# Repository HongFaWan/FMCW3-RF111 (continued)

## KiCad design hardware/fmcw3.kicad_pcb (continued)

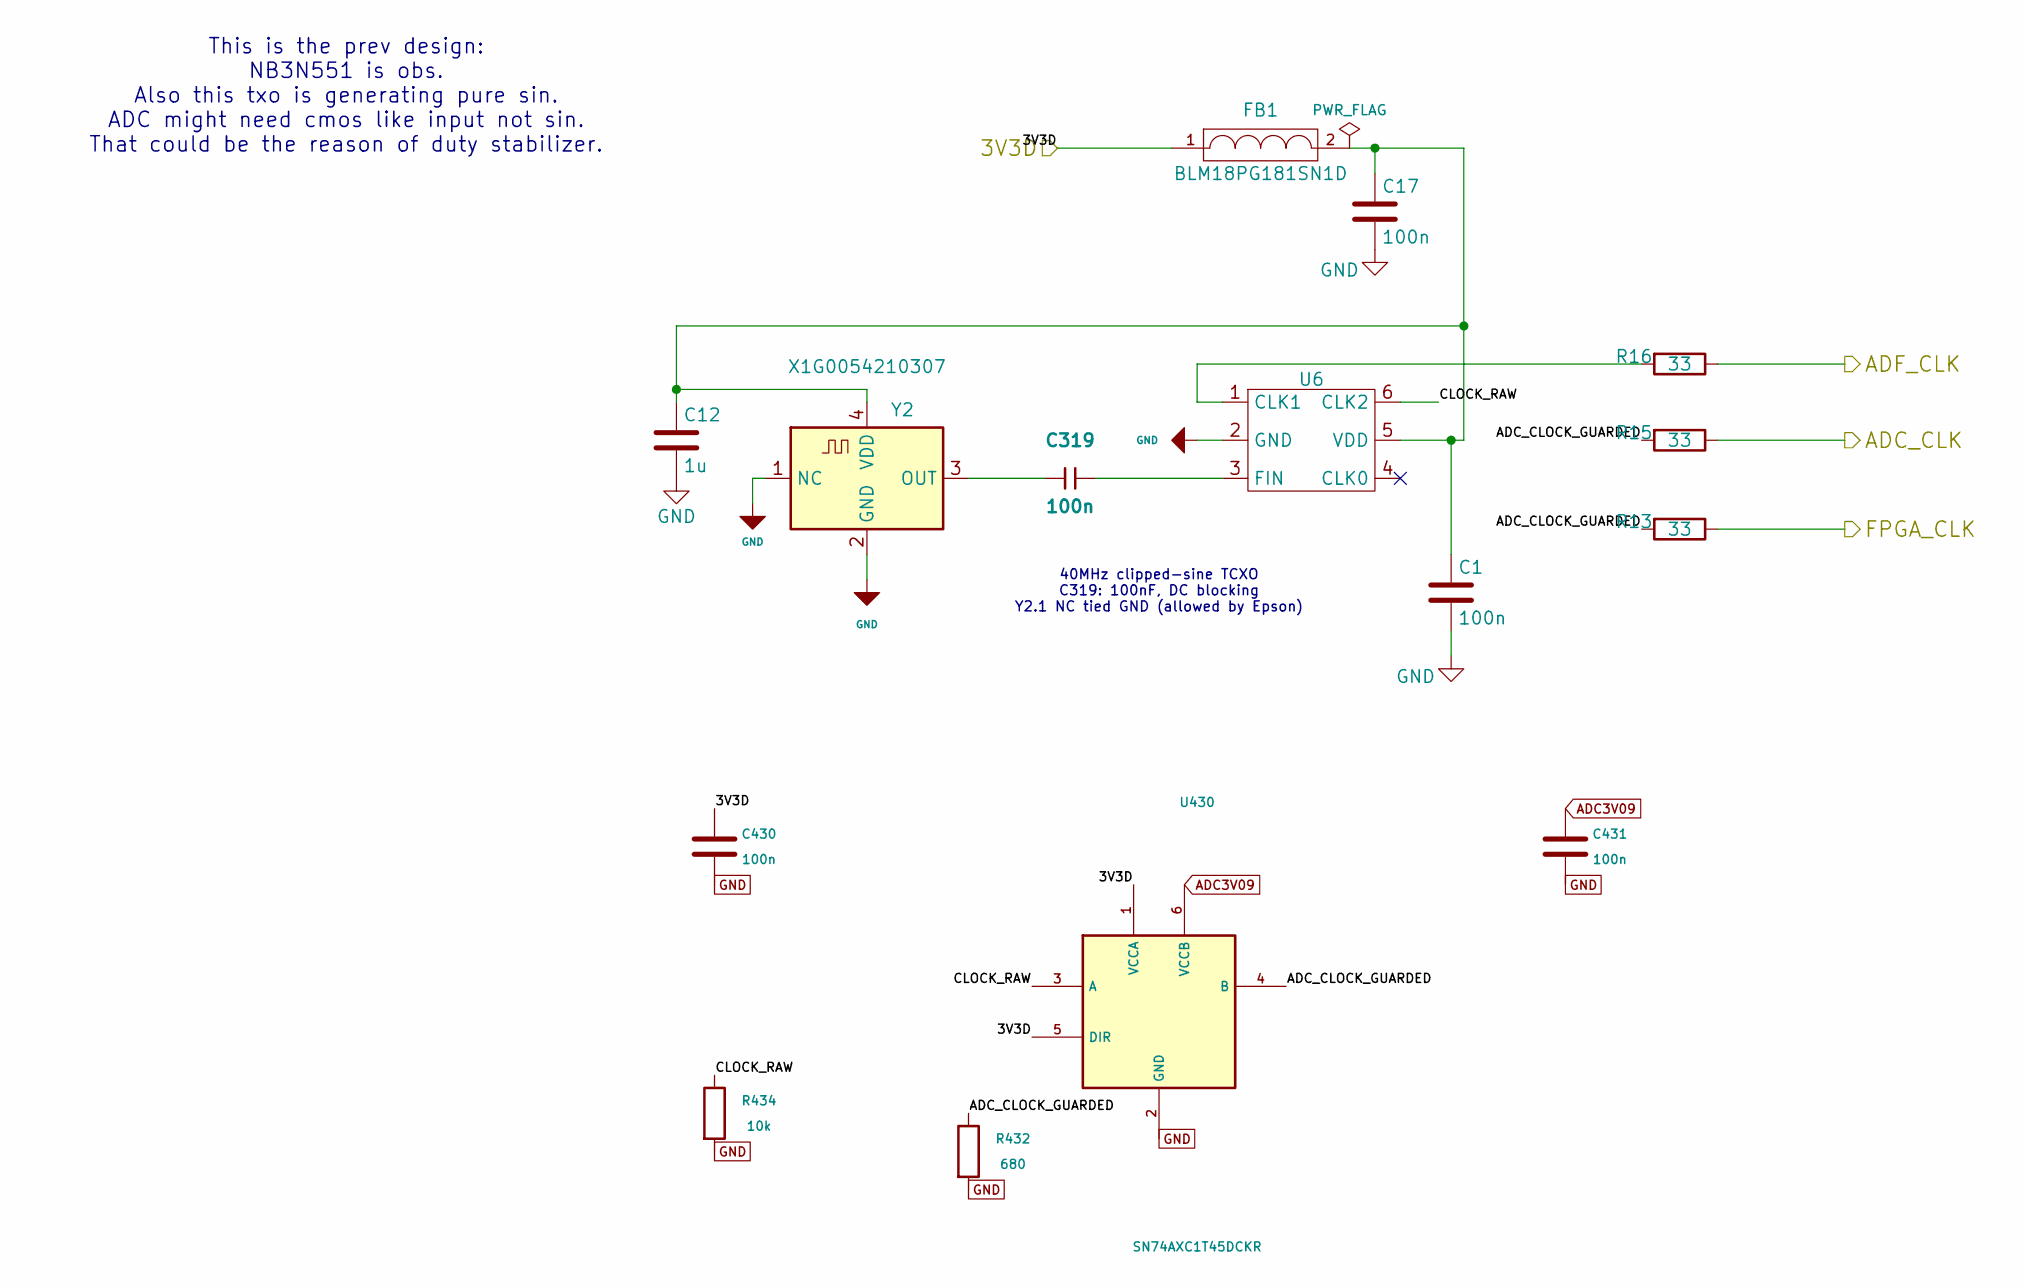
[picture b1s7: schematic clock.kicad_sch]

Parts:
C1, C17, C319: 100n; SMD_0402
C12: 1u; SMD_0603
C430, C431: 100n; SMD_0402; Voltage 50V; Tolerance 10%; MPN GRM155R71H104KE14D; LCSC C77020
FB1: BLM18PG181SN1D; SMD_0603
R13, R15, R16: 33; SMD_0402
R432: 680; R0402_Yageo_Mount_V10; MPN RC0402FR-07680RL; LCSC C137948
R434: 10k; R0402_Yageo_Mount_V10; MPN RT0402BRD0710KL; LCSC C190095
U6: PL133-37; SOT23_6
U430: SN74AXC1T45DCKR; TI_DCK6_0p9x0p4_MFR; MPN SN74AXC1T45DCKR; LCSC C2677392
Y2: X1G0054210307; TG2520SMN_MFR

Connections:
/ADC_CLK: R15.1; also elsewhere on the board
/ADF_CLK_REF: R16.1; also elsewhere on the board
/FPGA_CLK: R13.1; also elsewhere on the board
/clock/ADC_CLOCK_GUARDED: R13.2, R15.2, R432.1, U430.4 (B)
/clock/CLOCK_RAW: R434.1, U6.6 (CLK2), U430.3 (A)
ADC3V09: C431.1, U430.6 (VCCB); also elsewhere on the board
GND: C1.2, C12.2, C17.2, C430.2, C431.2, R432.2, R434.2, U6.2 (GND), U430.2 (GND), Y2.1 (NC), Y2.2 (GND); also elsewhere on the board
unnamed: R16.2, U6.1 (CLK1)
unnamed: C319.2, U6.3 (FIN)
unnamed: C1.1, C12.1, C17.1, FB1.2, U6.5 (VDD), Y2.4 (VDD)
unnamed: C319.1, Y2.3 (OUT)

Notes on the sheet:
40MHz clipped-sine TCXO C319: 100nF, DC blocking Y2.1 NC tied GND (allowed by Epson)
This is the prev design: NB3N551 is obs. Also this txo is generating pure sin. ADC might need cmos like input not sin. That could be the reason of duty stabilizer.

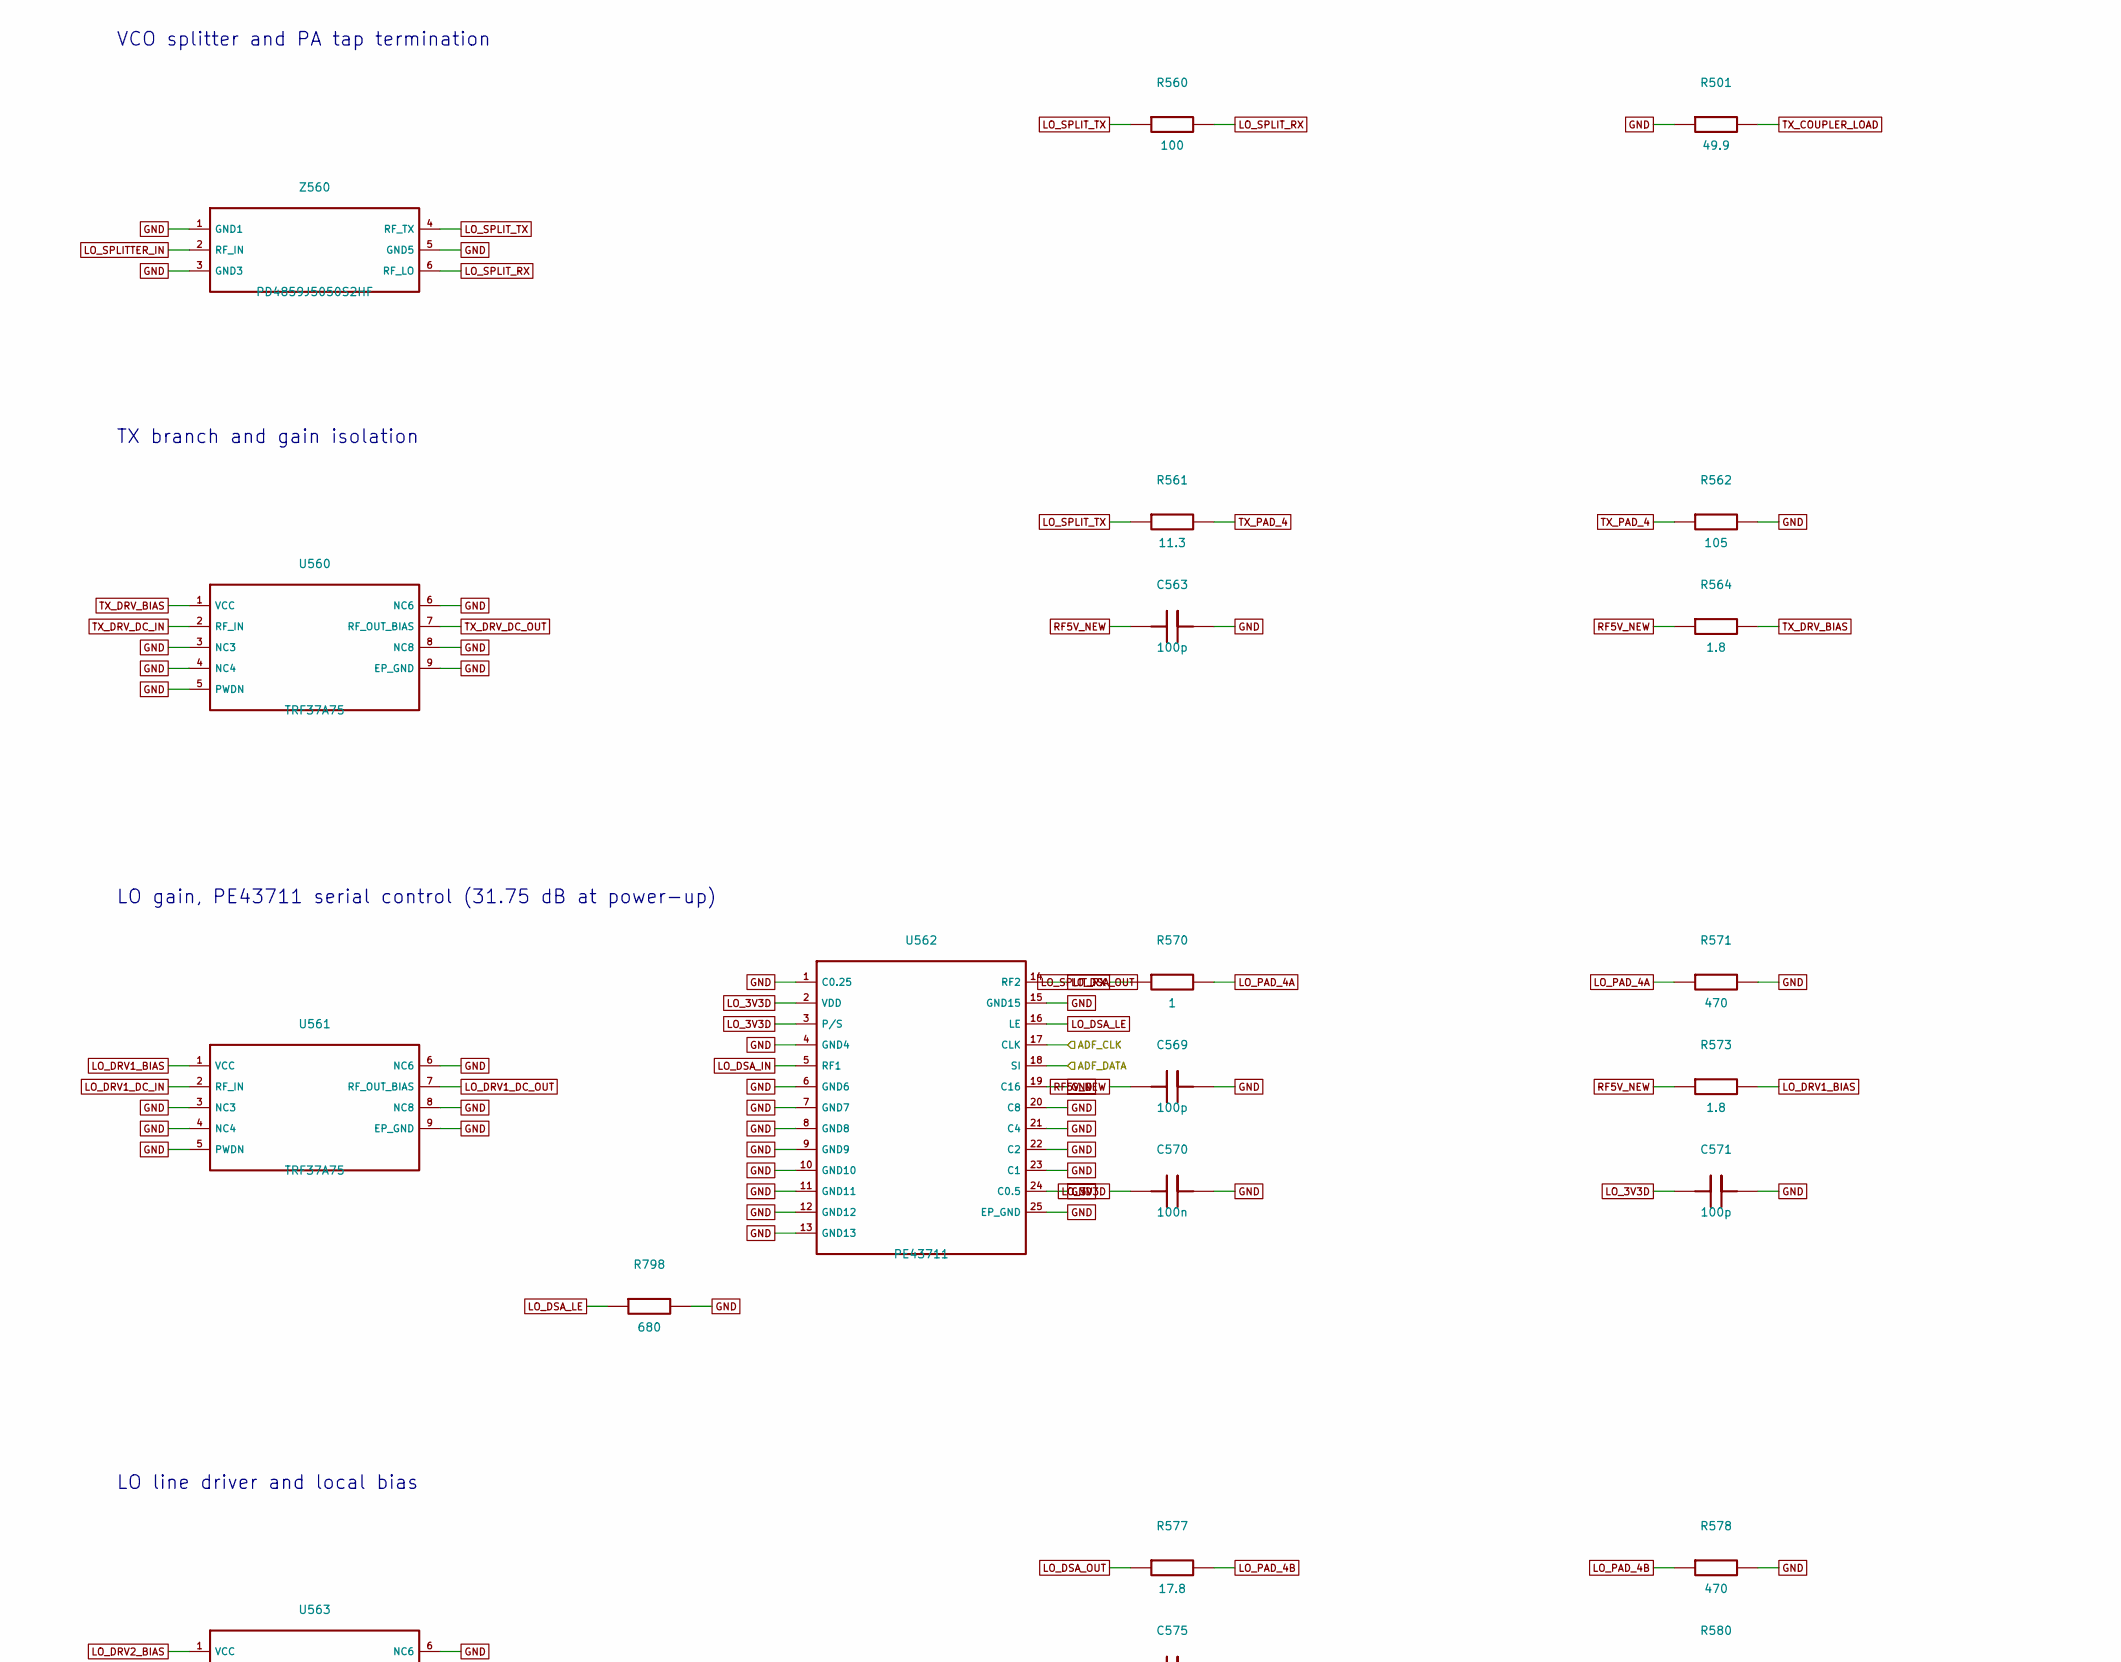
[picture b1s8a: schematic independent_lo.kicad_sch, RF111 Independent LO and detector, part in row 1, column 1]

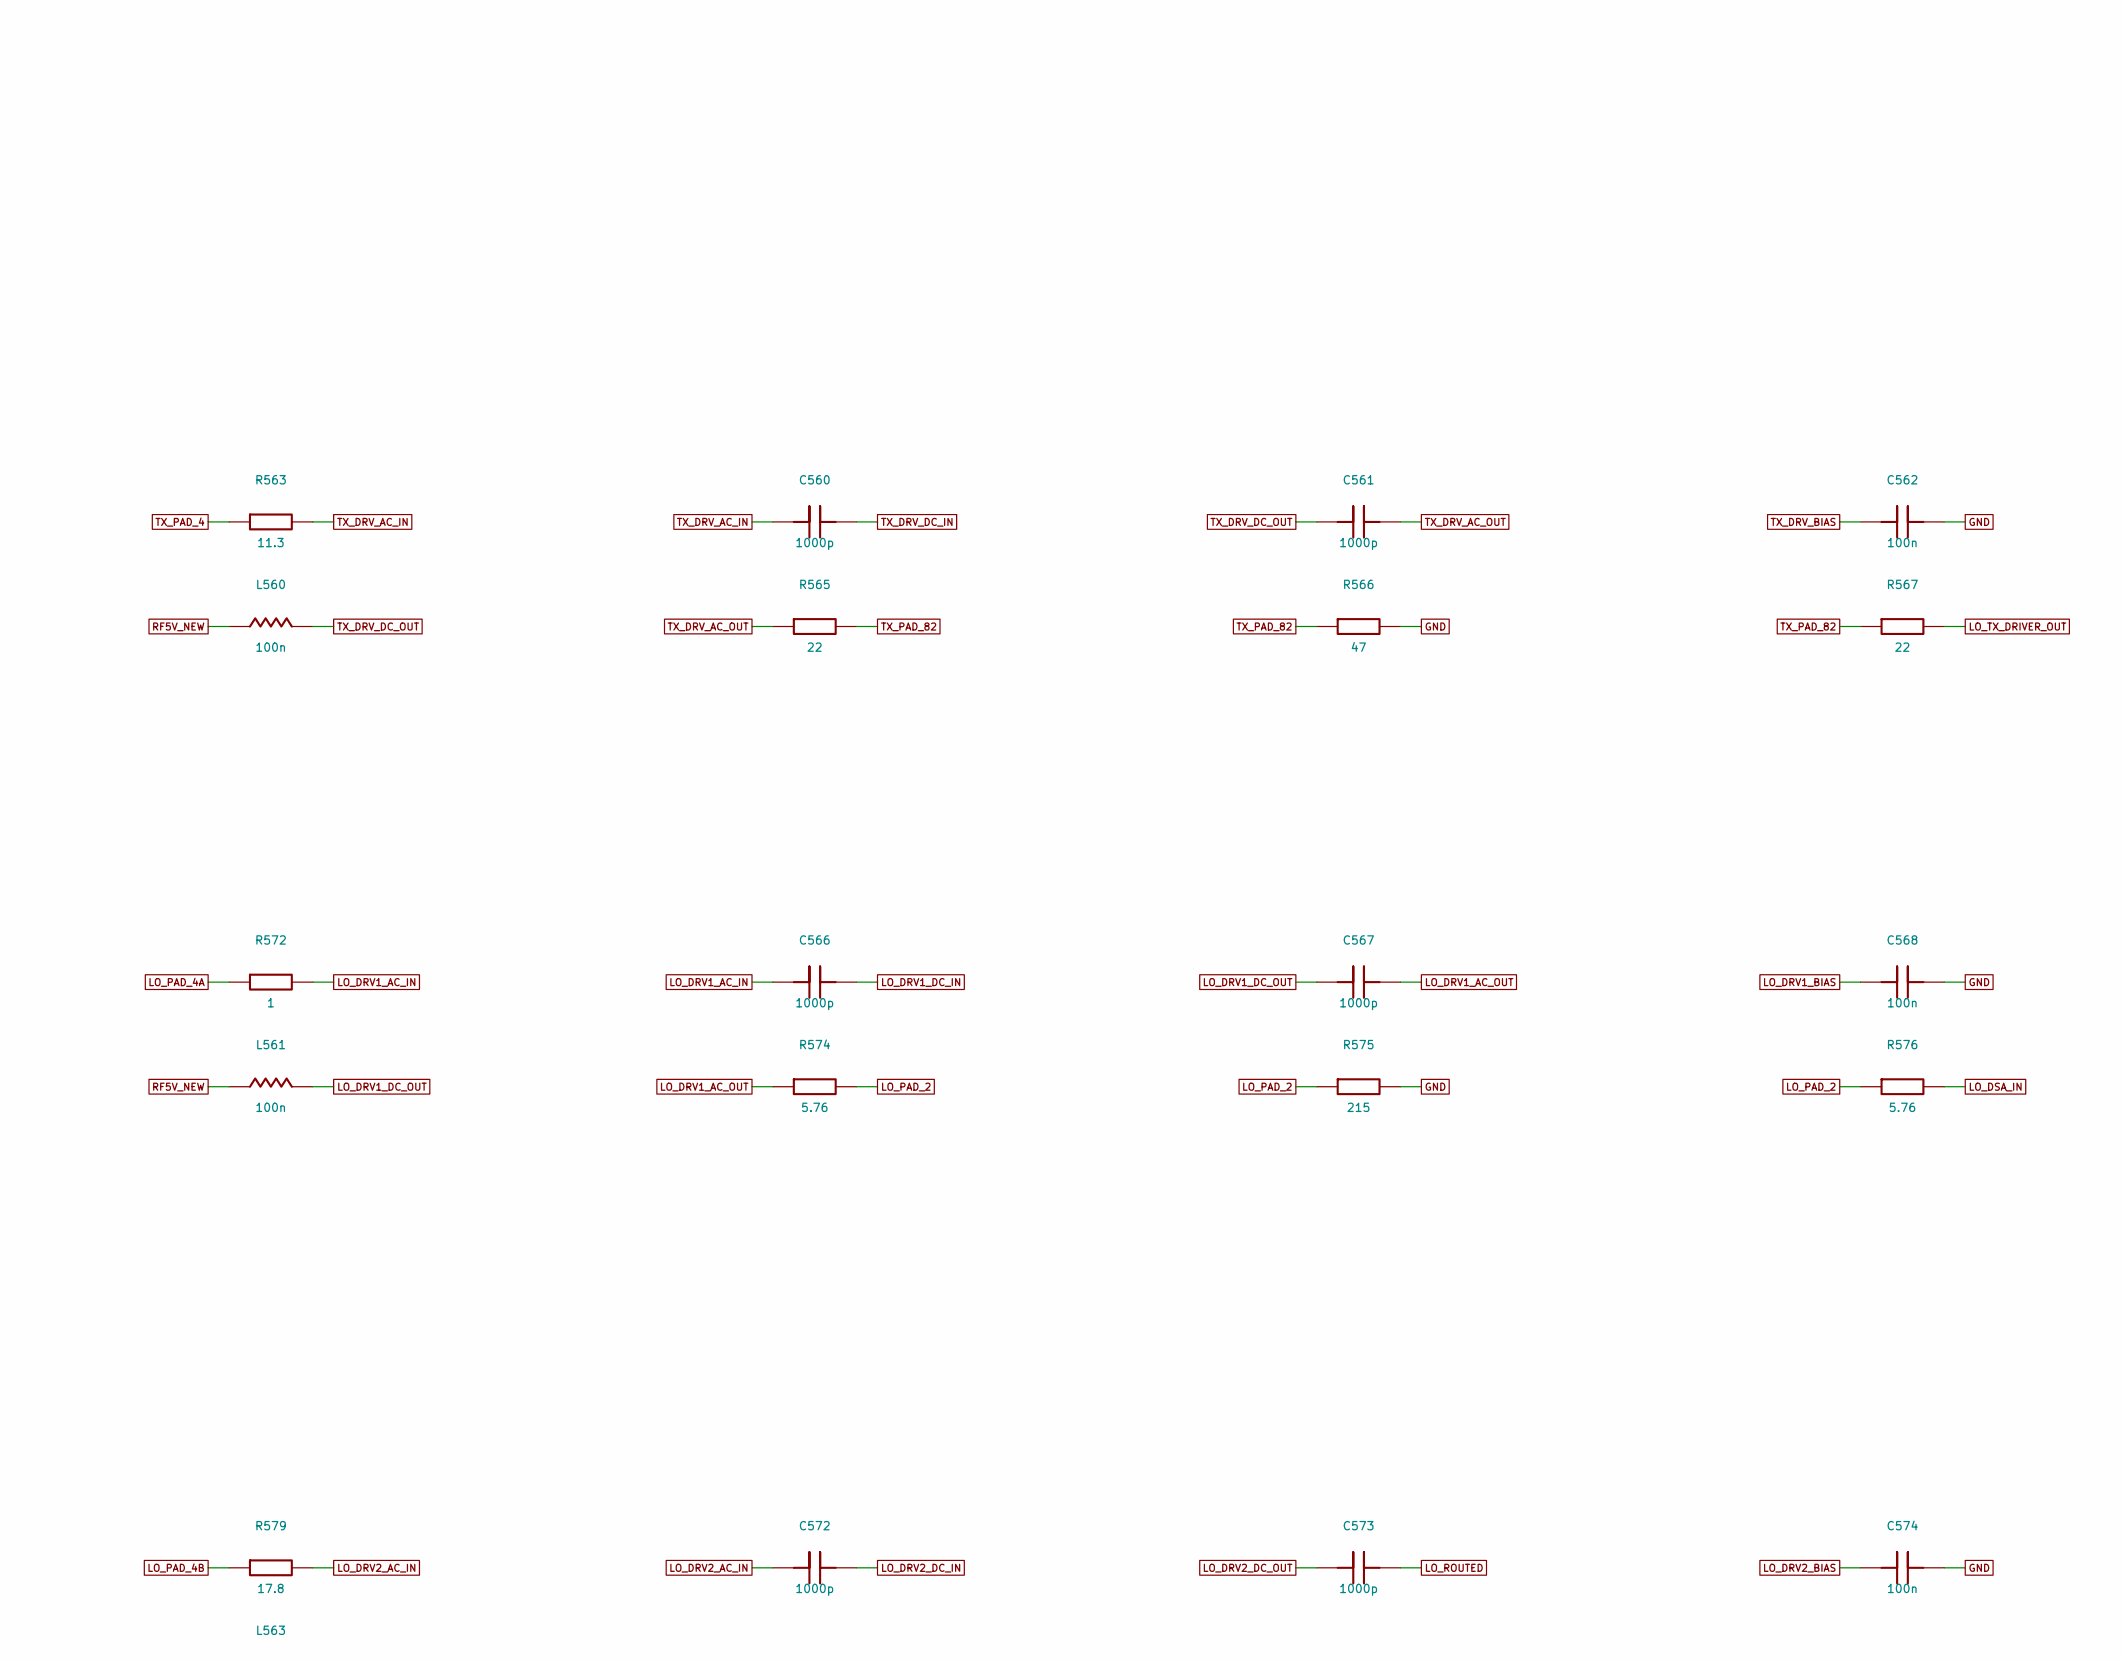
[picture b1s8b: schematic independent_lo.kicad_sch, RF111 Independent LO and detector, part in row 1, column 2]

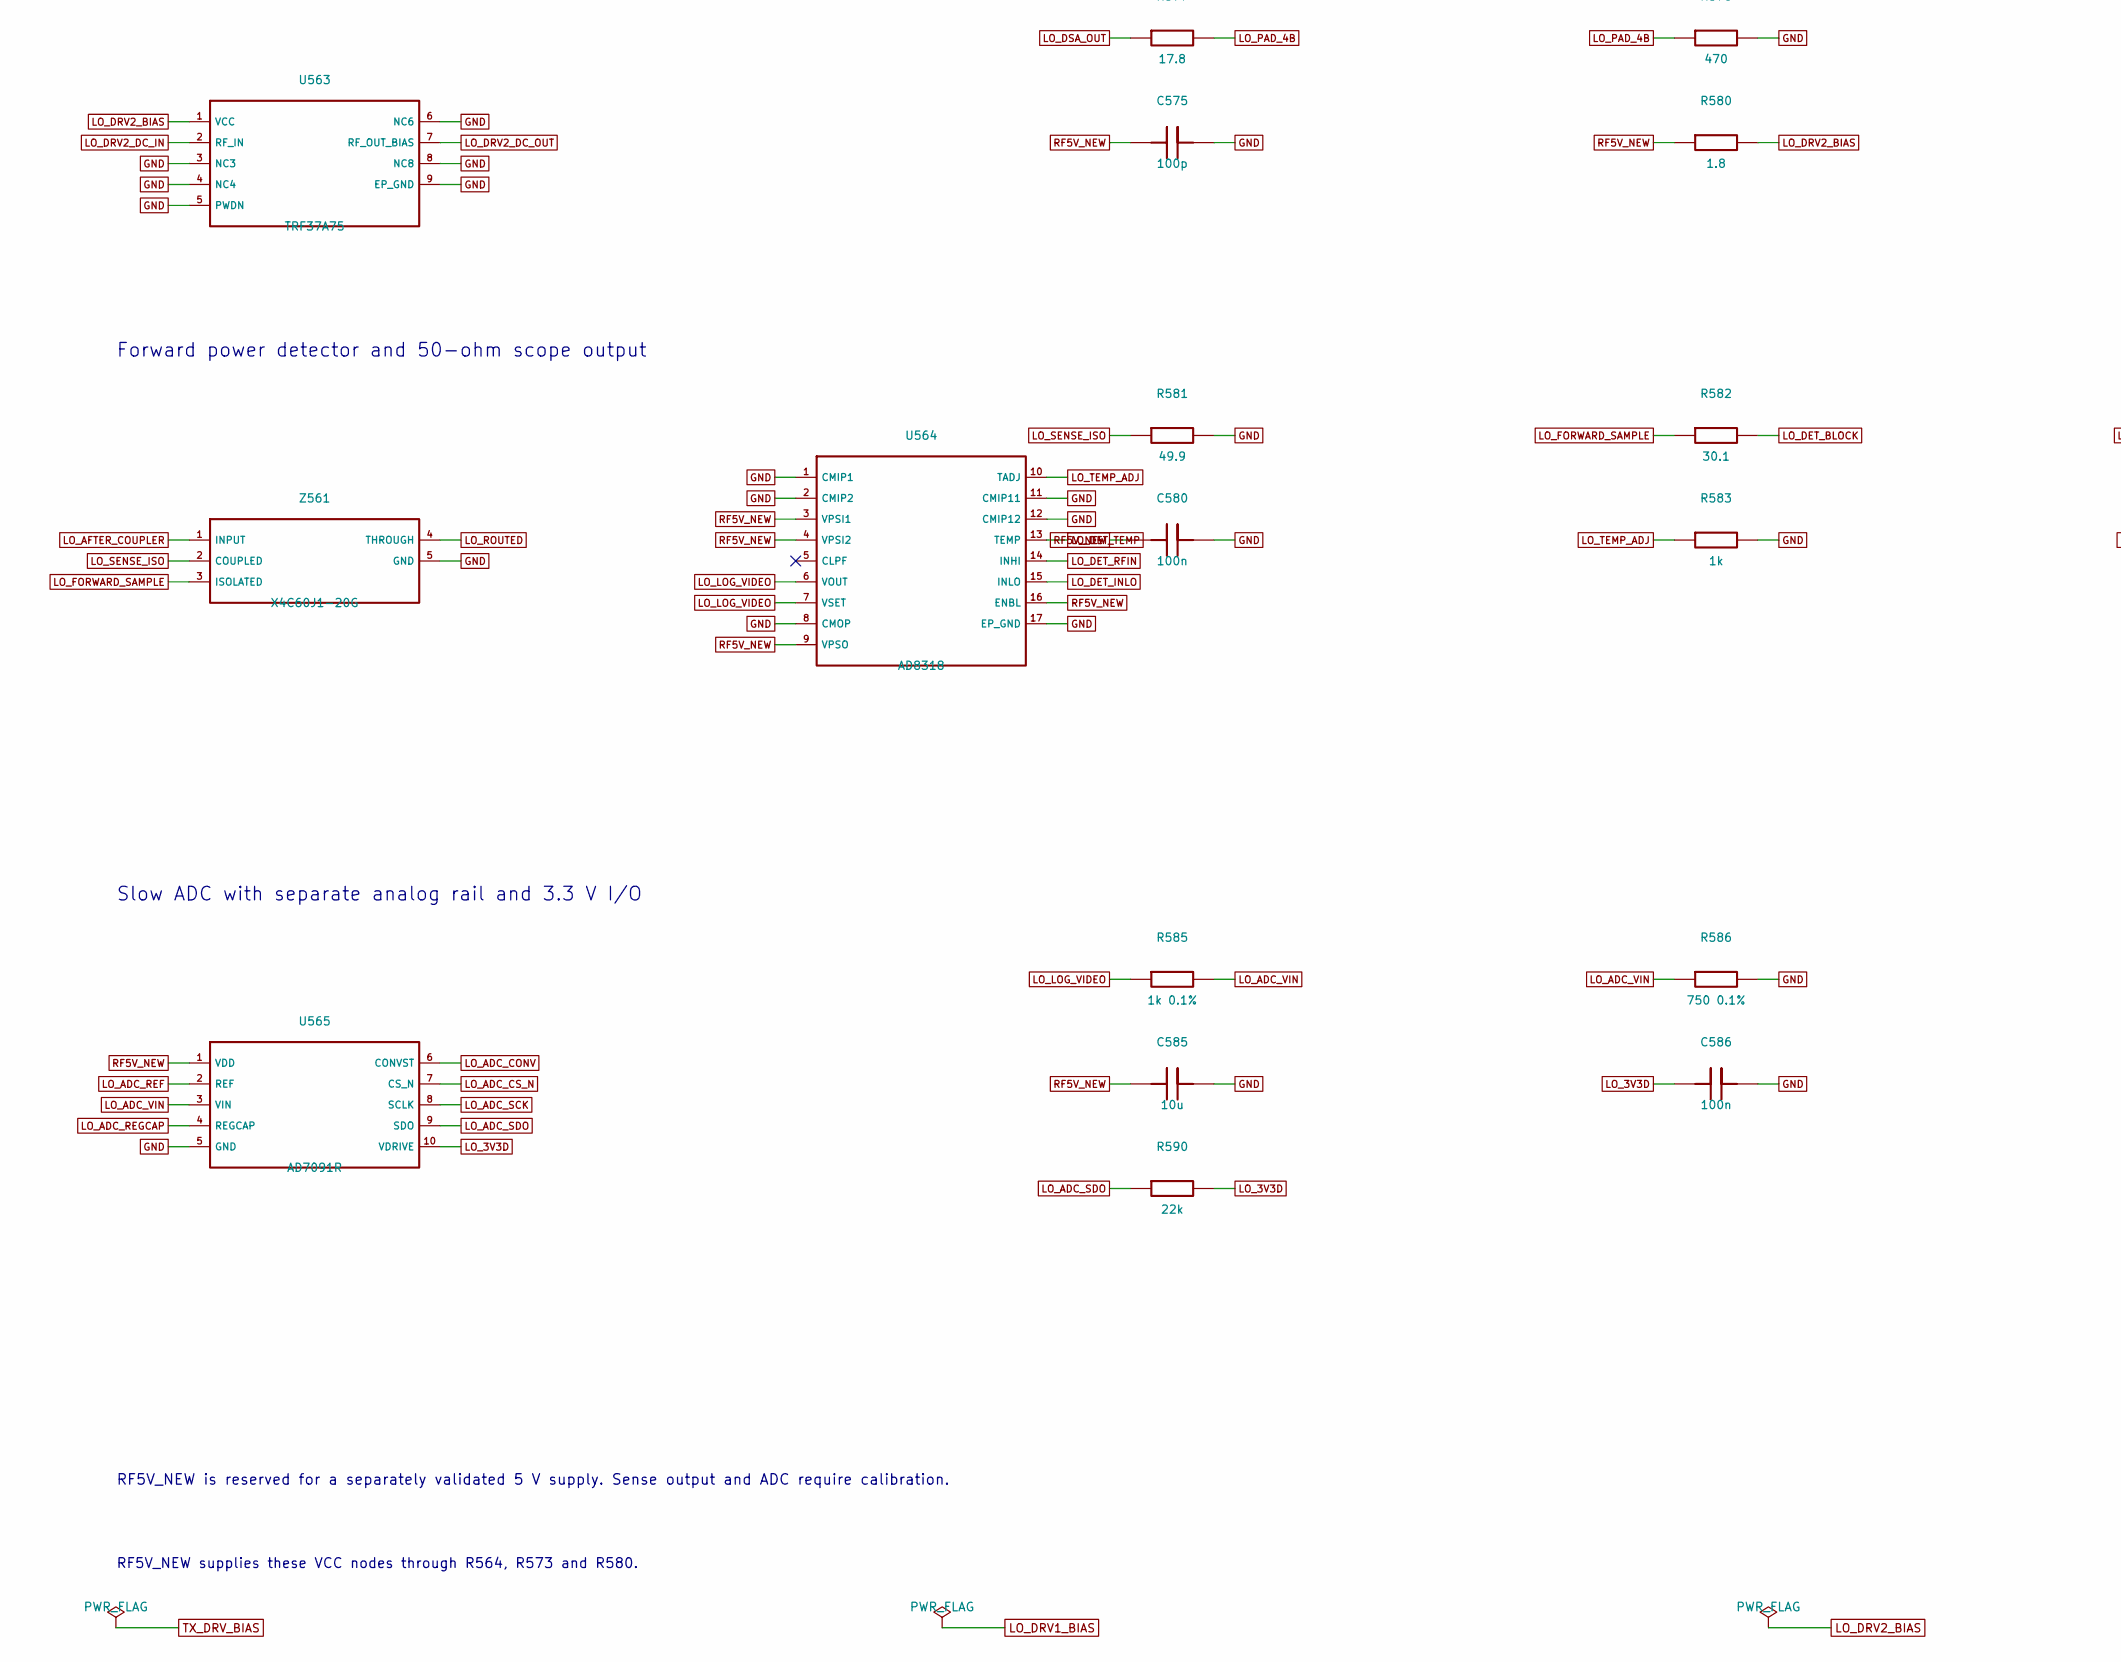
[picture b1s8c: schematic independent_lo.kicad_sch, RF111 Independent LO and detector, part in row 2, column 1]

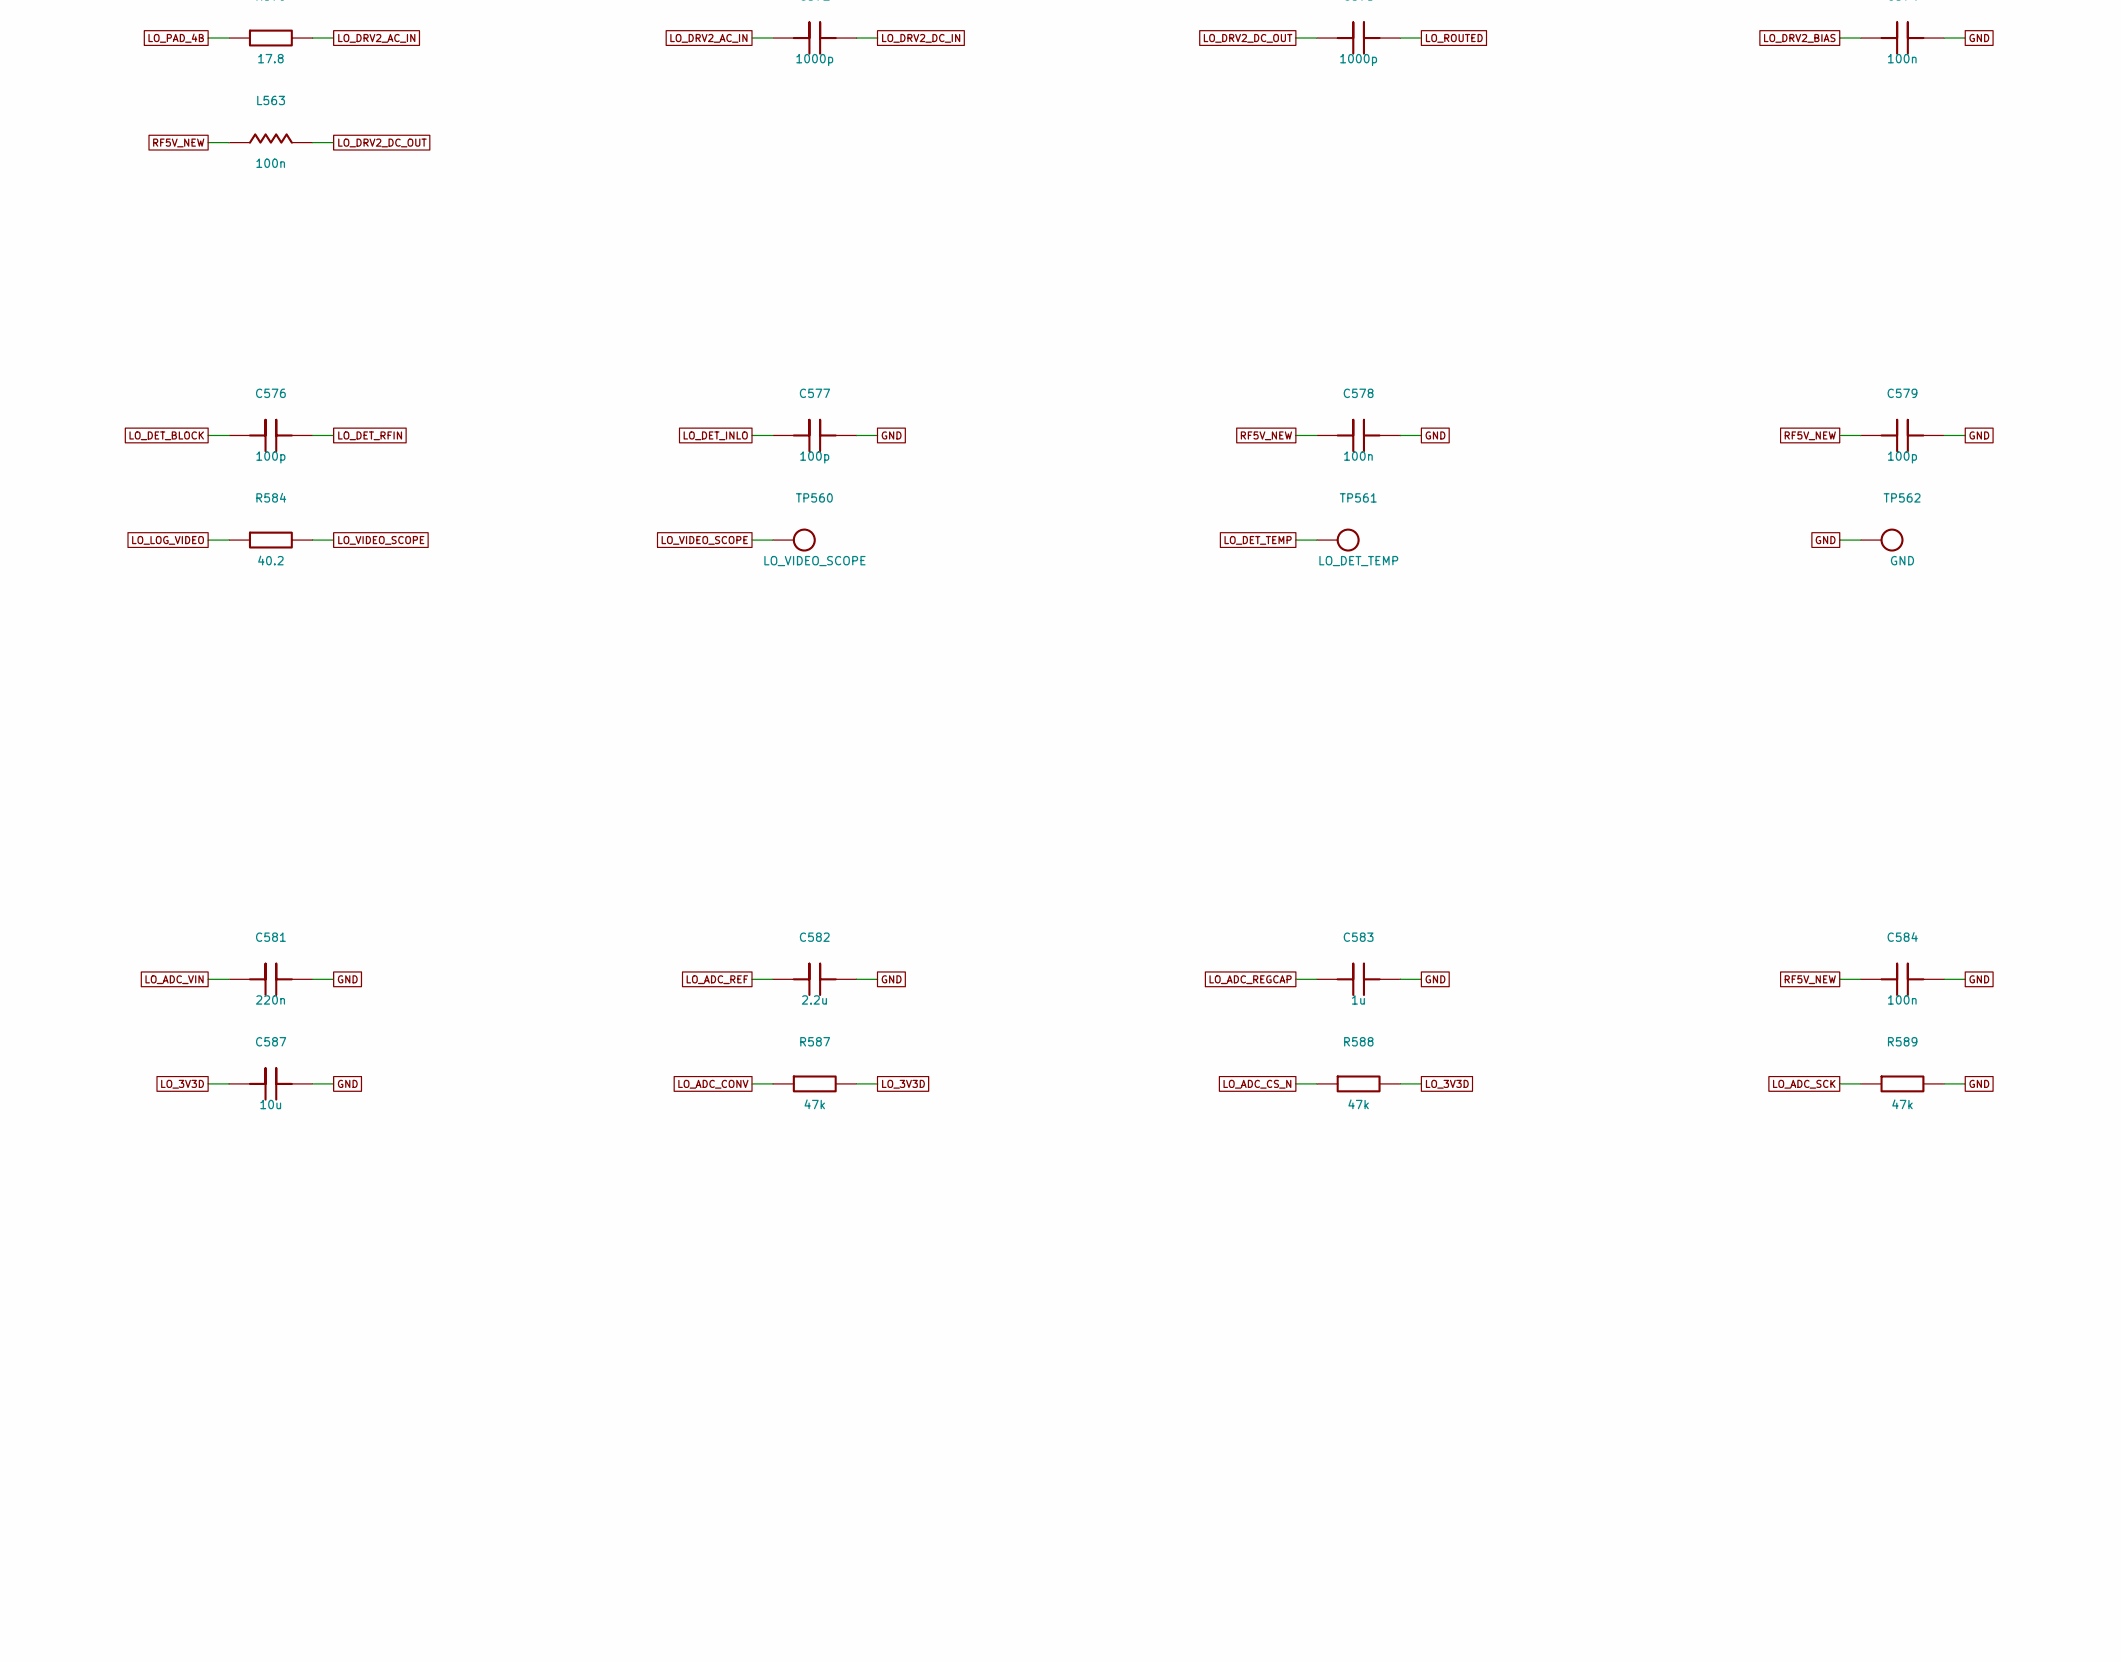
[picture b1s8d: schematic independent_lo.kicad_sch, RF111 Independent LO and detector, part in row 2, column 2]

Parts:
C560, C561, C566, C567, C572, C573: 1000p; C_0402_1005Metric; MPN GRM1555C1H102JA01D
C562, C568, C570, C574, C578, C580, C584, C586: 100n; C_0402_1005Metric; MPN GRM155R71H104KE14D
C563, C569, C571, C575, C576, C577, C579: 100p; C_0402_1005Metric; MPN GRM1555C1H101JA01D
C581: 220n; C_0402_1005Metric; MPN GRM155R71C224KA12D
C582: 2.2u; C_0603_1608Metric; MPN GRM188R71A225KE15D
C583: 1u; C_0603_1608Metric; MPN GRM188R71A105KA61D
C585, C587: 10u; C_0805_2012Metric; MPN GRM21BR61E106KA73L
L560, L561, L563: 100n; L_0402_1005Metric; MPN 0402HPH-R10XGRW
R501: 49.9; SMD_0402; MPN RC0402FR-0749R9L
R560: 100; R_0603_1608Metric; MPN RC0603FR-07100RL
R561, R563: 11.3; R_0402_1005Metric; MPN RC0402FR-0711R3L
R562: 105; R_0402_1005Metric; MPN RC0402FR-07105RL
R564, R573, R580: 1.8; R_0402_1005Metric; MPN RC0402FR-071R8L
R565, R567: 22; R_0402_1005Metric; MPN RC0402FR-0722RL
R566: 47; R_0402_1005Metric; MPN RT0402BRD0747RL
R570, R572: 1; R_0402_1005Metric; MPN RC0402FR-071RL
R571, R578: 470; R_0402_1005Metric; MPN RC0402FR-07470RL
R574, R576: 5.76; R_0402_1005Metric; MPN RC0402FR-075R76L
R575: 215; R_0402_1005Metric; MPN RC0402FR-07215RL
R577, R579: 17.8; R_0402_1005Metric; MPN RC0402FR-0717R8L
R581: 49.9; R_0402_1005Metric; MPN RC0402FR-0749R9L
R582: 30.1; R_0402_1005Metric; MPN RC0402FR-0730R1L
R583: 1k; R_0402_1005Metric; MPN RT0402BRD071KL
R584: 40.2; R_0402_1005Metric; MPN RC0402FR-0740R2L
R585: 1k 0.1%; R_0402_1005Metric; MPN ERA-2AEB102X
R586: 750 0.1%; R_0402_1005Metric; MPN ERA-2AEB751X
R587, R588, R589: 47k; R_0402_1005Metric; MPN RC0402FR-0747KL
R590: 22k; R_0402_1005Metric; MPN RC0402FR-0722KL
R798: 680; R_0402_Yageo_Mount22; MPN RC0402FR-07680RL; LCSC C137948
TP560: LO_VIDEO_SCOPE; TestPoint_Pad_D1.0mm
TP561: LO_DET_TEMP; TestPoint_Pad_D1.0mm
TP562: GND; TestPoint_Pad_D1.0mm
U560, U561, U563: TRF37A75; TI_DSG0008A; MPN TRF37A75IDSGR
U562: PE43711; pSemi_PE43711_QFN24; MPN PE43711B-Z
U564: AD8318; ADI_CP-16-59; MPN AD8318ACPZ-REEL7
U565: AD7091R; MSOP-10_3x3mm_P0.5mm; MPN AD7091RBRMZ-RL7
Z560: PD4859J5050S2HF; MPN PD4859J5050S2HF
Z561: X4C60J1-20G; MPN X4C60J1-20G

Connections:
/ADF_CLK: U562.17 (CLK); also elsewhere on the board
/ADF_DATA: U562.18 (SI); also elsewhere on the board
GND: C562.2, C563.2, C568.2, C569.2, C570.2, C571.2, C574.2, C575.2, C577.2, C578.2, C579.2, C580.2, C581.2, C582.2, C583.2, C584.2, C585.2, C586.2, C587.2, R501.1, R562.2, R566.2, R571.2, R575.2, R578.2, R581.2, R583.2, R586.2, R589.2, R798.2, TP562.1, U560.3 (NC3), U560.4 (NC4), U560.5 (PWDN), U560.6 (NC6), U560.8 (NC8), U560.9 (EP_GND), U561.3 (NC3), U561.4 (NC4), U561.5 (PWDN), U561.6 (NC6), U561.8 (NC8), U561.9 (EP_GND), U562.1 (C0.25), U562.4 (GND4), U562.6 (GND6), U562.7 (GND7), U562.8 (GND8), U562.9 (GND9), U562.10 (GND10), U562.11 (GND11), U562.12 (GND12), U562.13 (GND13), U562.15 (GND15), U562.19 (C16), U562.20 (C8), U562.21 (C4), U562.22 (C2), U562.23 (C1), U562.24 (C0.5), U562.25 (EP_GND), U563.3 (NC3), U563.4 (NC4), U563.5 (PWDN), U563.6 (NC6), U563.8 (NC8), U563.9 (EP_GND), U564.1 (CMIP1), U564.2 (CMIP2), U564.8 (CMOP), U564.11 (CMIP11), U564.12 (CMIP12), U564.17 (EP_GND), U565.5 (GND), Z560.1 (GND1), Z560.3 (GND3), Z560.5 (GND5), Z561.5 (GND); also elsewhere on the board
LO_ADC_CONV: R587.1, U565.6 (CONVST); also elsewhere on the board
LO_ADC_CS_N: R588.1, U565.7 (CS_N); also elsewhere on the board
LO_ADC_REF: C582.1, U565.2 (REF)
LO_ADC_REGCAP: C583.1, U565.4 (REGCAP)
LO_ADC_SCK: R589.1, U565.8 (SCLK); also elsewhere on the board
LO_ADC_SDO: R590.1, U565.9 (SDO); also elsewhere on the board
LO_ADC_VIN: C581.1, R585.2, R586.1, U565.3 (VIN)
LO_AFTER_COUPLER: Z561.1 (INPUT); also elsewhere on the board
LO_DET_BLOCK: C576.1, R582.2
LO_DET_INLO: C577.1, U564.15 (INLO)
LO_DET_RFIN: C576.2, U564.14 (INHI)
LO_DET_TEMP: TP561.1, U564.13 (TEMP)
LO_DRV1_AC_IN: C566.1, R572.2
LO_DRV1_AC_OUT: C567.2, R574.1
LO_DRV1_BIAS: C568.1, R573.2, U561.1 (VCC)
LO_DRV1_DC_IN: C566.2, U561.2 (RF_IN)
LO_DRV1_DC_OUT: C567.1, L561.2, U561.7 (RF_OUT_BIAS)
LO_DRV2_AC_IN: C572.1, R579.2
LO_DRV2_BIAS: C574.1, R580.2, U563.1 (VCC)
LO_DRV2_DC_IN: C572.2, U563.2 (RF_IN)
LO_DRV2_DC_OUT: C573.1, L563.2, U563.7 (RF_OUT_BIAS)
LO_DSA_IN: R576.2, U562.5 (RF1)
LO_DSA_LE: R798.1, U562.16 (LE); also elsewhere on the board
LO_DSA_OUT: R577.1, U562.14 (RF2)
LO_FORWARD_SAMPLE: R582.1, Z561.3 (ISOLATED)
LO_LOG_VIDEO: R584.1, R585.1, U564.6 (VOUT), U564.7 (VSET)
LO_PAD_2: R574.2, R575.1, R576.1
LO_PAD_4A: R570.2, R571.1, R572.1
LO_PAD_4B: R577.2, R578.1, R579.1
LO_ROUTED: C573.2, Z561.4 (THROUGH)
LO_SENSE_ISO: R581.1, Z561.2 (COUPLED)
LO_SPLITTER_IN: Z560.2 (RF_IN); also elsewhere on the board
LO_SPLIT_RX: R560.2, R570.1, Z560.6 (RF_LO)
LO_SPLIT_TX: R560.1, R561.1, Z560.4 (RF_TX)
LO_TEMP_ADJ: R583.1, U564.10 (TADJ)
LO_TX_DRIVER_OUT: R567.2; also elsewhere on the board
LO_VIDEO_SCOPE: R584.2, TP560.1
RF5V_NEW: C563.1, C569.1, C575.1, C578.1, C579.1, C580.1, C584.1, C585.1, L560.1, L561.1, L563.1, R564.1, R573.1, R580.1, U564.3 (VPSI1), U564.4 (VPSI2), U564.9 (VPSO), U564.16 (ENBL), U565.1 (VDD); also elsewhere on the board
TX_COUPLER_LOAD: R501.2; also elsewhere on the board
TX_DRV_AC_IN: C560.1, R563.2
TX_DRV_AC_OUT: C561.2, R565.1
TX_DRV_BIAS: C562.1, R564.2, U560.1 (VCC)
TX_DRV_DC_IN: C560.2, U560.2 (RF_IN)
TX_DRV_DC_OUT: C561.1, L560.2, U560.7 (RF_OUT_BIAS)
TX_PAD_4: R561.2, R562.1, R563.1
TX_PAD_82: R565.2, R566.1, R567.1

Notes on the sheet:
VCO splitter and PA tap termination
TX branch and gain isolation
LO gain, PE43711 serial control (31.75 dB at power-up)
LO line driver and local bias
Forward power detector and 50-ohm scope output
Slow ADC with separate analog rail and 3.3 V I/O
RF5V_NEW is reserved for a separately validated 5 V supply. Sense output and ADC require calibration.
RF5V_NEW supplies these VCC nodes through R564, R573 and R580.

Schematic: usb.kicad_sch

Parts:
C152, C153, C154, C158, C159, C160, C161, C207, C210, C211, C212: 100n; SMD_0402
C155, C156, C157: 4.7u; SMD_0603
C208, C209: 15p; SMD_0402
C690: 100nF; C_0402_1005Metric
FB12, FB14: BLM18PG181SN1D; SMD_0603
J1: USB_C_Receptacle_USB2.0; USB_C_Receptacle_GCT_USB4105-xx-A_16P_TopMnt_Horizontal
R3, R8: 5.1k; SMD_0402
R71: 12k; SMD_0402
R72: 1k; SMD_0402
R73, R83: 10k; SMD_0402
R79: 2.2k; SMD_0402
R80, R81: 0; SMD_0402
R82: 4.7k; SMD_0402
R84, R85, R88: 33; SMD_0402
R690: 4.7k; R_0402_1005Metric
R691: 22k; R_0402_1005Metric
U32: 93LC46B; SOT-23-6
U33: FT2232H; LQFP-64_10x10mm_Pitch0.5mm
U690: SN74LVC1G17DCKR; SOT-353_SC-70-5
Y1: ABM10-167-12.000MHZ-T3; ABM10

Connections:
/fpga/CLKOUT: U33.32 (ACBUS5); also elsewhere on the board
/fpga/FT_D0: U33.16 (ABUS0); also elsewhere on the board
/fpga/FT_D1: U33.17 (ABUS1); also elsewhere on the board
/fpga/FT_D2: U33.18 (ABUS2); also elsewhere on the board
/fpga/FT_D3: U33.19 (ABUS3); also elsewhere on the board
/fpga/FT_D4: U33.21 (ABUS4); also elsewhere on the board
/fpga/FT_D5: U33.22 (ABUS5); also elsewhere on the board
/fpga/FT_D6: U33.23 (ABUS6); also elsewhere on the board
/fpga/FT_D7: U33.24 (ABUS7); also elsewhere on the board
/fpga/FT_SUSPEND: U33.36 (SUSPEND#); also elsewhere on the board
/fpga/FT_TCK: R84.1; also elsewhere on the board
/fpga/FT_TDI: R88.1; also elsewhere on the board
/fpga/FT_TDO: U33.40 (BDBUS2); also elsewhere on the board
/fpga/FT_TMS: R85.1; also elsewhere on the board
/fpga/OE#: U33.33 (ACBUS6); also elsewhere on the board
/fpga/RD#: U33.28 (ACBUS2); also elsewhere on the board
/fpga/RXF#: U33.26 (ACBUS0); also elsewhere on the board
/fpga/SIWUA: U33.30 (ACBUS4); also elsewhere on the board
/fpga/TXE#: U33.27 (ACBUS1); also elsewhere on the board
/fpga/WR: U33.29 (ACBUS3); also elsewhere on the board
/fpga/usb/1V8: C152.1, C153.1, C154.1, C156.1, U33.12 (VCORE), U33.37 (VCORE), U33.49 (VREGOUT), U33.64 (VCORE)
/fpga/usb/DO: R73.2, R79.1, U32.1 (DO)
/fpga/usb/EECLK: U32.4 (CLK), U33.62 (EECLK)
/fpga/usb/EECS: U32.5 (CS), U33.63 (EECS)
/fpga/usb/EEDATA: R79.2, U32.3 (DI), U33.61 (EEDATA)
/fpga/usb/USBDM: J1.A7 (D-), J1.B7 (D-), R80.2
/fpga/usb/USBDP: J1.A6 (D+), J1.B6 (D+), R81.2
/fpga/usb/USB_5V: J1.A4 (VBUS), J1.A9 (VBUS), J1.B4 (VBUS), J1.B9 (VBUS), R82.1
/fpga/usb/USB_FTDI_SENSE: R690.2, U33.59 (BCBUS7)
/fpga/usb/USB_SENSE_BUF: R690.1, U690.4
/fpga/usb/USB_VBUS_DIV: R82.2, R83.1, U690.2
FTDI_RESET_N: R72.1, U33.14 (RESET#); also elsewhere on the board
GND: C152.2, C153.2, C154.2, C155.2, C156.2, C157.2, C158.2, C159.2, C160.2, C161.2, C207.2, C208.2, C209.2, C210.2, C211.2, C212.2, C690.2, J1.A1 (GND), J1.A12 (GND), J1.B1 (GND), J1.B12 (GND), J1.S1 (SHIELD), R3.2, R8.2, R71.2, R83.2, R691.2, U32.2 (VSS), U33.1 (GND), U33.5 (GND), U33.10 (AGND), U33.11 (GND), U33.13 (TEST), U33.15 (GND), U33.25 (GND), U33.35 (GND), U33.47 (GND), U33.51 (GND), U690.3 (GND), Y1.2, Y1.4; also elsewhere on the board
unnamed: J1.A5 (CC1), R3.1
unnamed: J1.B5 (CC2), R8.1
unnamed: R84.2, U33.38 (BDBUS0)
unnamed: R88.2, U33.39 (BDBUS1)
unnamed: R85.2, U33.41 (BDBUS3)
unnamed: R80.1, U33.7 (DM)
unnamed: R81.1, U33.8 (DP)
unnamed: C208.1, U33.2 (OSCI), Y1.1
unnamed: C209.1, U33.3 (OSCO), Y1.3
unnamed: R71.1, U33.6 (REF)
unnamed: C155.1, C211.1, FB12.2, U33.4 (VPHY)
unnamed: C157.1, C212.1, FB14.2, U33.9 (VPLL)
